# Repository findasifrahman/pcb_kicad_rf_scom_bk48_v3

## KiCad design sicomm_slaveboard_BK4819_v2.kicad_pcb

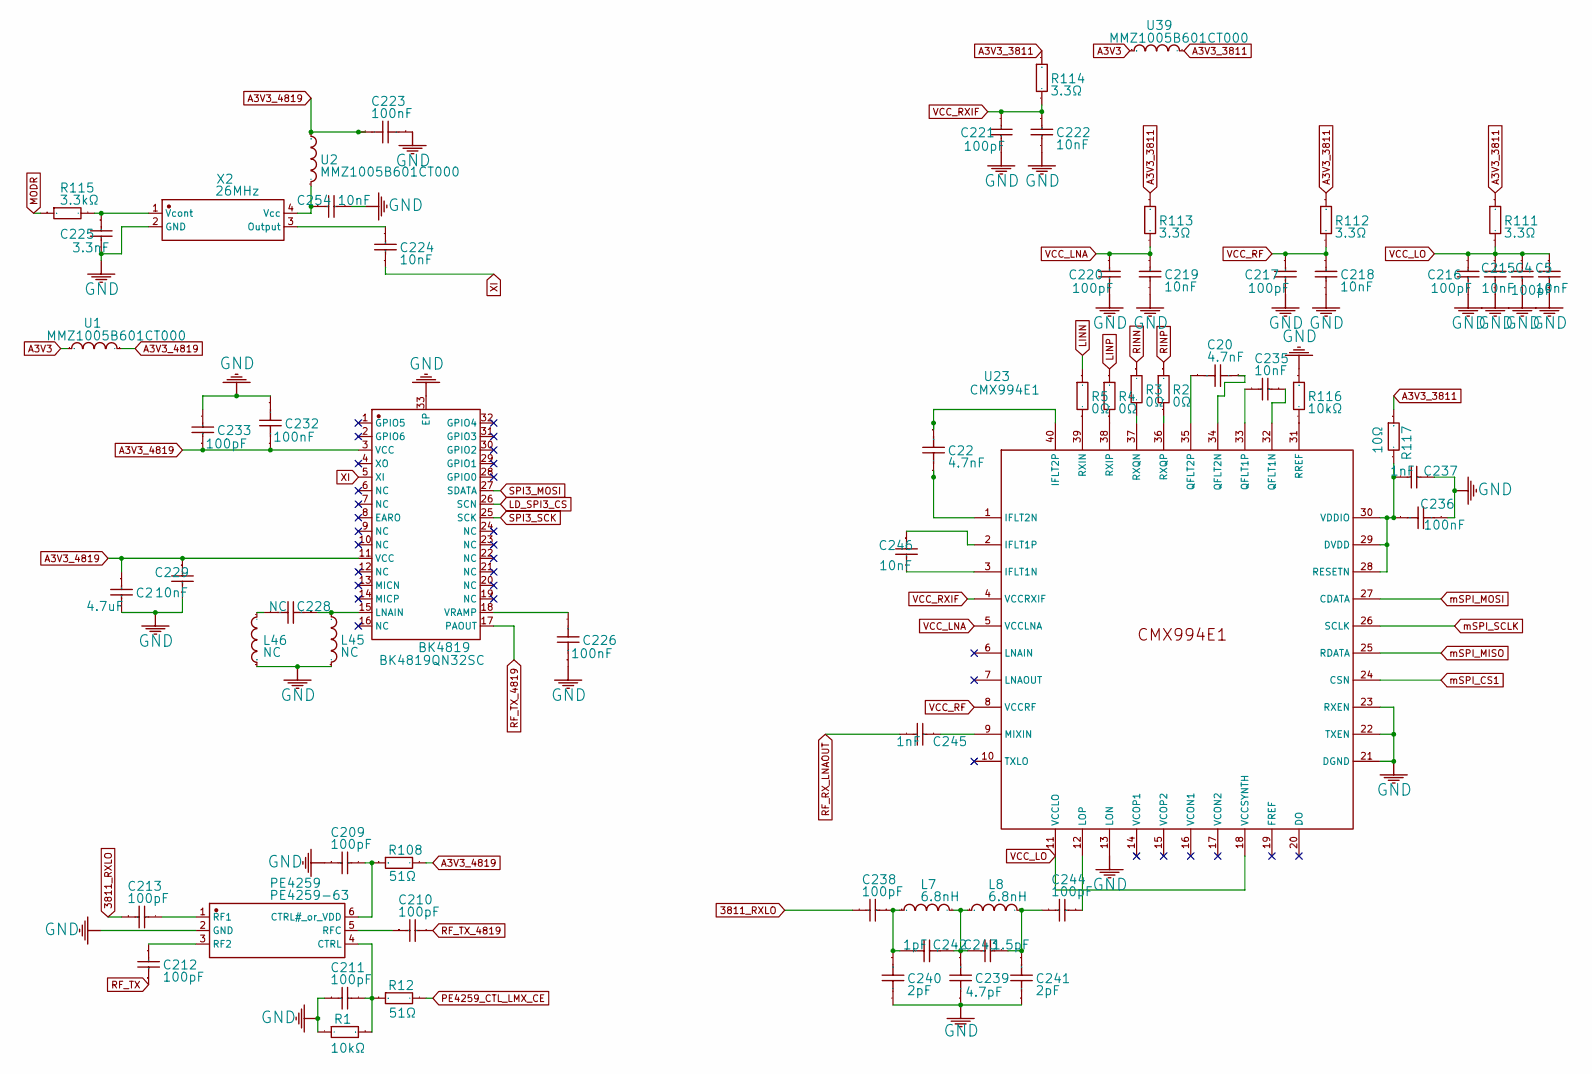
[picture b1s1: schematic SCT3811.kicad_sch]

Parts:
BK4819: BK4819QN32SC; QFN-32_L4.0-W4.0-P0.40-TL-EP2.9; Manufacturer Part BK4819QN32SC
C2: 4.7uF; C0402; Manufacturer Part CL05A475MP5NRNC
C4, C209, C210, C211, C212, C213, C216, C217, C220, C221, C233, C238, C244: 100pF; C0402
C5, C215, C218, C219, C222, C235, C246: 10nF; C0402; Manufacturer Part GRM1555C1E103JE01D
C20, C22: 4.7nF; C0402; Manufacturer Part GRM1557U1A472JA01D
C223, C226, C232, C236: 100nF; C0402
C224, C229, C254: 10nF; C0402
C225: 3.3nF; C0603; Manufacturer Part CL10B332KB8NNNC
C228: NC; C0402
C237, C245: 1nF; C0402
C239: 4.7pF; C0402
C240, C241: 2pF; C0402
C242: 1pF; C0402
C243: 1.5pF; C0402
L7, L8: 6.8nH; IND-SMD_L1.0-W0.5-2; Manufacturer Part LQW15AN6N8H00D
L45, L46: NC; L0402
PE4259: PE4259-63; SC-70-6_L2.2-W1.3-P0.65-LS2.1-BL; Manufacturer Part PE4259-63
R1, R116: 10kΩ; R0402
R2, R3, R4, R5: 0Ω; R0402
R12, R108: 51Ω; R0603; Manufacturer Part 0603WAF510JT5E
R111, R112, R113, R114: 3.3Ω; R0402; Manufacturer Part RC0402JR-073R3L
R115: 3.3kΩ; R0402; Manufacturer Part 0402WGF3301TCE
R117: 10Ω; C0402
U1, U2, U39: MMZ1005B601CT000; L0402; Manufacturer Part MMZ1005B601CT000
U23: CMX994E1; QFN50P600X600X100-41N-D
X2: 26MHz; OSC-SMD_4P-L3.2-W2.5-BL_1XTV; Manufacturer Part 1XTV26000PEA

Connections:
3811_RXLO: C213.1, C238.2
A3V3: U1.1, U39.1; also elsewhere on the board
A3V3_3811: R111.1, R112.1, R113.1, R117.1, U39.2; also elsewhere on the board
A3V3_4819: BK4819.3 (VCC), BK4819.11 (VCC), C2.1, C223.2, C229.1, C232.1, C233.1, R108.2, U1.2, U2.1
GND: BK4819.33 (EP), C2.2, C4.1, C5.2, C209.1, C211.1, C215.2, C216.1, C217.1, C218.2, C219.2, C220.1, C221.1, C222.2, C223.1, C225.2, C226.1, C229.2, C232.2, C233.2, C236.2, C237.1, C239.2, C240.2, C241.2, C254.2, L45.2, L46.1, PE4259.2 (GND), R1.2, R116.1, U23.13 (LON), U23.21 (DGND), U23.22 (TXEN), U23.23 (RXEN), U23.41, X2.2 (GND); also elsewhere on the board
LD_SPI3_CS: BK4819.26 (SCN); also elsewhere on the board
LINN: R5.1; also elsewhere on the board
LINP: R4.1; also elsewhere on the board
MODR: R115.1; also elsewhere on the board
unnamed: BK4819.15 (LNAIN), C228.1, L45.1
unnamed: BK4819.18 (VRAMP), C226.2
unnamed 17: C239.1, C242.1, L7.2, L8.1; also elsewhere on the board
unnamed 18: C241.1, C244.2, L8.2; also elsewhere on the board
unnamed: C228.2, L46.2
unnamed: C238.1, C240.1, C242.2, L7.1
unnamed: C209.2, PE4259.6 (CTRL#_or_VDD), R108.1
unnamed: C211.2, PE4259.4 (CTRL), R1.1, R12.1
unnamed: C213.2, PE4259.1 (RF1)
unnamed: C212.2, PE4259.3 (RF2)
unnamed: C210.1, PE4259.5 (RFC)
unnamed: C236.1, C237.2, R117.2, U23.28 (RESETN), U23.29 (DVDD), U23.30 (VDDIO)
unnamed: C246.2, U23.3 (IFLT1N)
unnamed: C246.1, U23.2 (IFLT1P)
unnamed: C22.2, U23.1 (IFLT2N)
unnamed: C22.1, U23.40 (IFLT2P)
unnamed: C244.1, U23.12 (LOP)
unnamed: C245.1, U23.9 (MIXIN)
unnamed: C235.1, U23.32 (QFLT1N)
unnamed: C235.2, U23.33 (QFLT1P)
unnamed: C20.2, U23.34 (QFLT2N)
unnamed: C20.1, U23.35 (QFLT2P)
unnamed: R116.2, U23.31 (RREF)
unnamed: R5.2, U23.39 (RXIN)
unnamed: R4.2, U23.38 (RXIP)
unnamed: R3.2, U23.37 (RXQN)
unnamed: R2.2, U23.36 (RXQP)
unnamed 60: X2.3 (Output); also elsewhere on the board
unnamed: C254.1, U2.2, X2.4 (Vcc)
unnamed: C225.1, R115.2, X2.1 (Vcont)
PE4259_CTL_LMX_CE: R12.2; also elsewhere on the board
RF_RX_LNAOUT: C245.2; also elsewhere on the board
RF_TX: C212.1; also elsewhere on the board
RF_TX_4819: BK4819.17 (PAOUT), C210.2
RINN: R3.1; also elsewhere on the board
RINP: R2.1; also elsewhere on the board
SPI3_MOSI: BK4819.27 (SDATA); also elsewhere on the board
SPI3_SCK: BK4819.25 (SCK); also elsewhere on the board
VCC_LNA: C219.1, C220.2, R113.2, U23.5 (VCCLNA)
VCC_LO: C4.2, C5.1, C215.1, C216.2, R111.2, U23.11 (VCCLO), U23.18 (VCCSYNTH)
VCC_RF: C217.2, C218.1, R112.2, U23.8 (VCCRF)
VCC_RXIF: C221.2, C222.1, U23.4 (VCCRXIF); also elsewhere on the board
XI: BK4819.5 (XI); also elsewhere on the board
mSPI_CS1: U23.24 (CSN); also elsewhere on the board
mSPI_MISO: U23.25 (RDATA); also elsewhere on the board
mSPI_MOSI: U23.27 (CDATA); also elsewhere on the board
mSPI_SCLK: U23.26 (SCLK); also elsewhere on the board

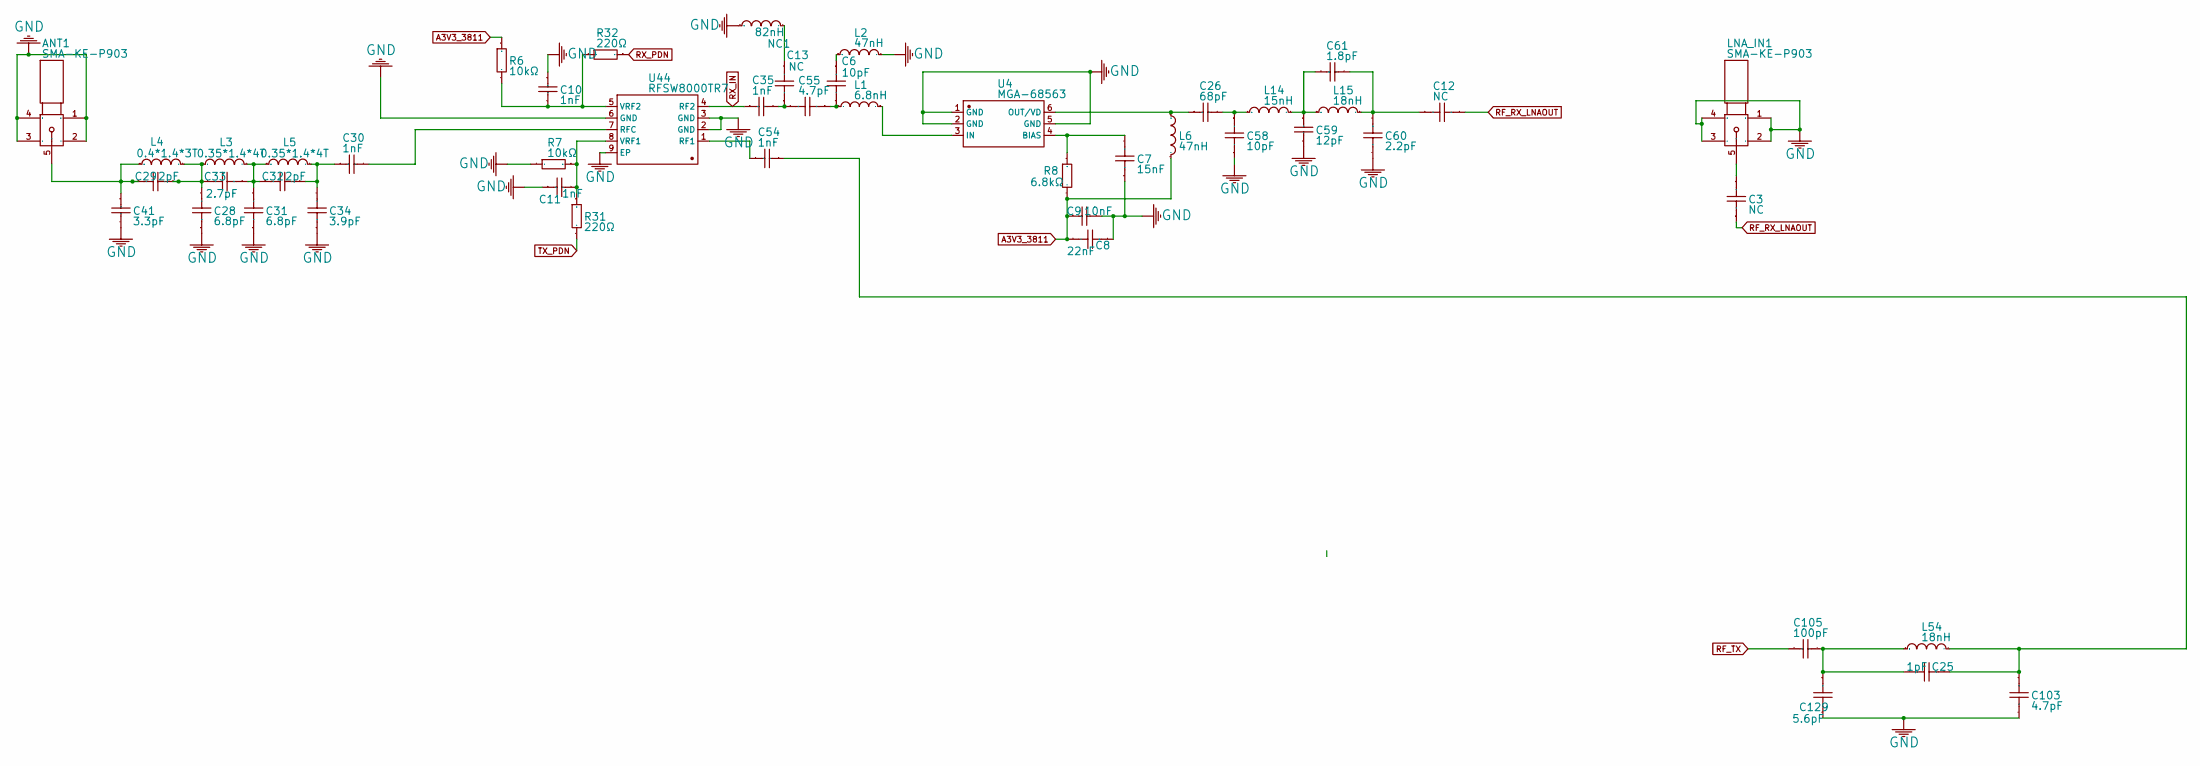
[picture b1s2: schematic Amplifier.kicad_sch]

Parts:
ANT1: SMA-KE-P903; SMA-TH_SMA-KE-P903
C3, C12: NC; C0402
C6, C58: 10pF; C0402
C7: 15nF; C0402; Manufacturer Part TCC0402X7R153K250AT
C8: 22nF; C0402; Manufacturer Part CL05B223KA5NNNC
C9: 10nF; C0402; Manufacturer Part GRM1555C1E103JE01D
C10, C11, C30, C35, C54: 1nF; C0402
C13: NC; C0603
C25: 1pF; C0402
C26: 68pF; C0402; Manufacturer Part GRM1555C1H680JA01D
C28, C31: 6.8pF; C0603; Manufacturer Part CC0603CRNPO9BN6R8
C29, C32: 2pF; C0402
C33: 2.7pF; C0603; Manufacturer Part 0603CG2R7C500NT
C34: 3.9pF; C0402
C41: 3.3pF; C0603; Manufacturer Part 0603CG3R3C500NT
C55, C103: 4.7pF; C0402
C59: 12pF; C0402
C60: 2.2pF; C0402; Manufacturer Part GJM1555C1H2R2CB01D
C61: 1.8pF; C0603; Manufacturer Part CL10C1R8BB8NNNC
C105: 100pF; C0402
C129: 5.6pF; C0402
L1: 6.8nH; IND-SMD_L1.6-W0.8-RD; Manufacturer Part LQW18AN6N8C10D
L2, L6: 47nH; IND-SMD_L1.6-W0.8-RD; Manufacturer Part LQG18HN47NJ00D
L3, L5: 0.35*1.4*4T; IND-SMD_L2.3-W1.7-1
L4: 0.4*1.4*3T; IND-SMD_L2.3-W1.7-1
L14: 15nH; IND-SMD_L1.0-W0.6
L15, L54: 18nH; IND-SMD_L1.6-W0.8-RD; Manufacturer Part LQG18HN18NJ00D
LNA_IN1: SMA-KE-P903; SMA-TH_SMA-KE-P903
NC1: 82nH; C0603; Manufacturer Part NC
R6, R7: 10kΩ; R0402
R8: 6.8kΩ; R0805; Manufacturer Part 0805W8F6801T5E
R31, R32: 220Ω; R0603; Manufacturer Part 0603WAF2200T5E
U4: MGA-68563; SOT-363_L2.0-W1.3-P0.65-LS2.1-BL; Manufacturer Part mga-68563
U44: RFSW8000TR7; DFN-8_L2.0-W2.0-P0.50-BL-EP; Manufacturer Part RFSW8000TR7

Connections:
A3V3_3811: C8.2, C9.1, L6.2, R6.1, R8.2; also elsewhere on the board
GND: ANT1.1, ANT1.2, ANT1.3, ANT1.4, C7.1, C8.1, C9.2, C10.1, C11.1, C28.1, C31.1, C34.1, C41.2, C58.2, C59.2, C60.2, C103.2, C129.2, L2.2, LNA_IN1.1, LNA_IN1.2, LNA_IN1.3, LNA_IN1.4, NC1.1, R7.2, U4.1 (GND), U4.2 (GND), U4.5 (GND), U44.2 (GND), U44.3 (GND), U44.6 (GND), U44.9 (EP); also elsewhere on the board
unnamed: ANT1.5, C29.1, C41.1, L4.1
unnamed: C3.2, LNA_IN1.5
unnamed: C6.1, L2.1
unnamed: C12.2, C60.1, C61.2, L15.2
unnamed: C13.1, C35.2, C55.2
unnamed: C13.2, NC1.2
unnamed: C26.2, C58.1, L14.1
unnamed: C28.2, C29.2, C33.1, L3.1, L4.2
unnamed: C30.1, C32.2, C34.2, L5.2
unnamed: C31.2, C32.1, C33.2, L3.2, L5.1
unnamed: C6.2, C55.1, L1.2
unnamed: C59.1, C61.1, L14.2, L15.1
unnamed: C25.1, C54.2, C103.1, L54.2
unnamed: C25.2, C105.2, C129.1, L54.1
unnamed: C7.2, R8.1, U4.4 (BIAS)
unnamed: L1.1, U4.3 (IN)
unnamed: C26.1, L6.1, U4.6 (OUT/VD)
unnamed: C54.1, U44.1 (RF1)
unnamed: C30.2, U44.7 (RFC)
unnamed: C11.2, R7.1, R31.1, U44.8 (VRF1)
unnamed: C10.2, R6.2, R32.2, U44.5 (VRF2)
RF_RX_LNAOUT: C3.1, C12.1; also elsewhere on the board
RF_TX: C105.1; also elsewhere on the board
RX_IN: C35.1, U44.4 (RF2)
RX_PDN: R32.1; also elsewhere on the board
TX_PDN: R31.2; also elsewhere on the board

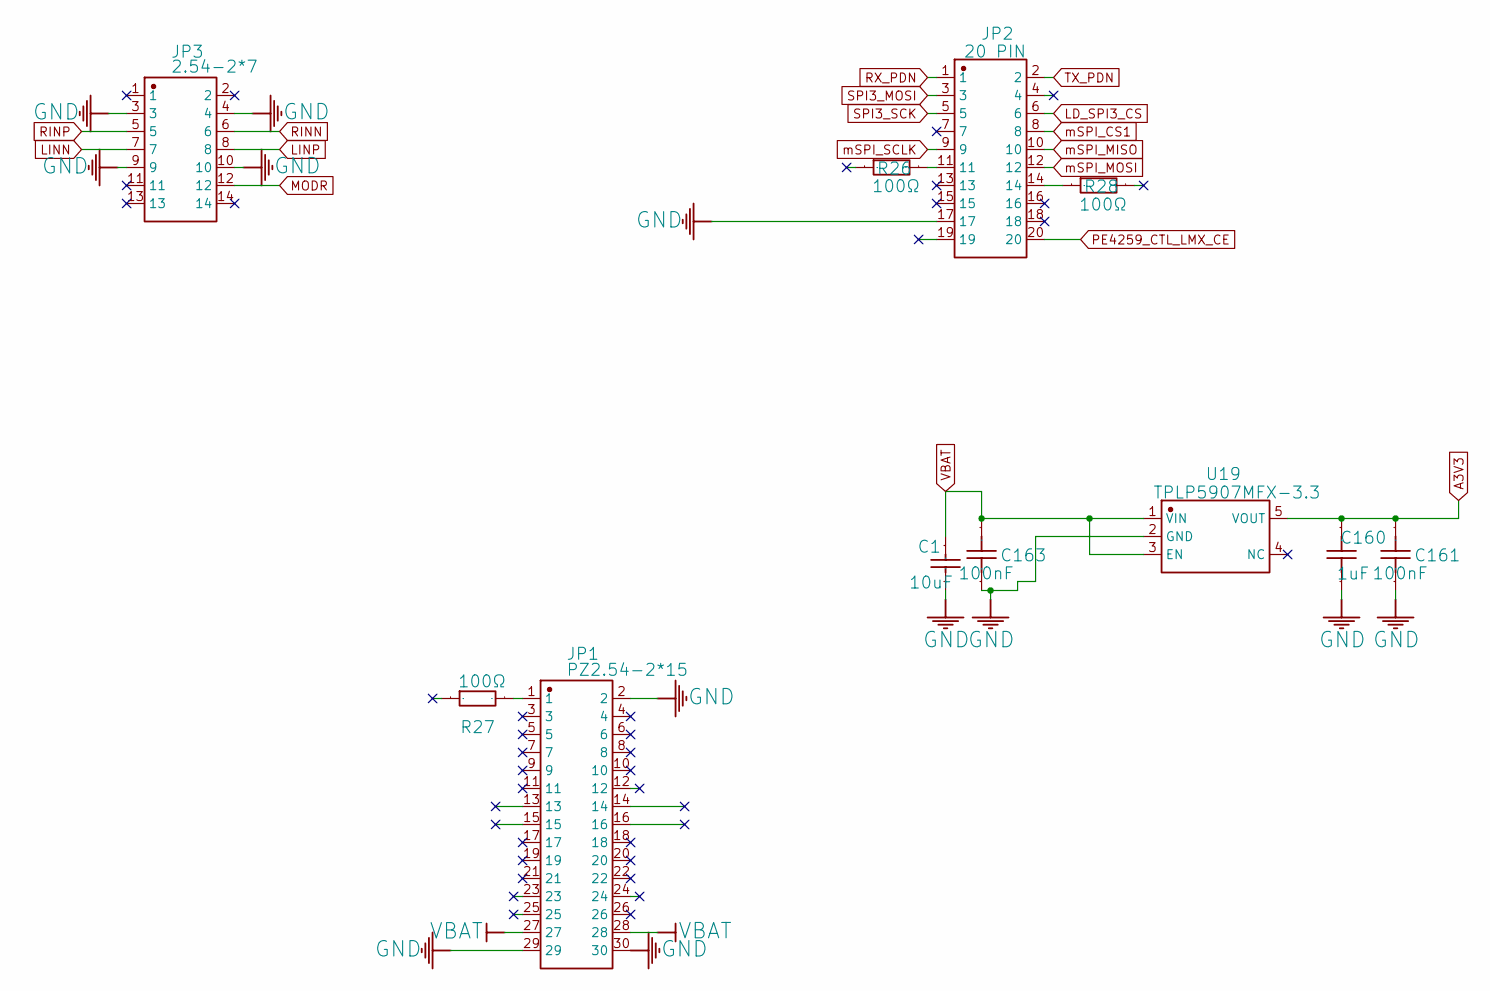
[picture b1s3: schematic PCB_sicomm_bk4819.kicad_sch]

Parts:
C1: 10uF; C0402; Manufacturer Part CL05A106MQ5NUNC
C160: 1uF; C0402
C161, C163: 100nF; C0402
JP1: PZ2.54-2*15; HDR-TH_30P-P2.54-V-M-R2-C15-S2.54-2; Manufacturer Part PZ2.54-2*15
JP2: 20 PIN; HDR-TH_20P-P2.54-V-M-R2-C10-S2.54; Manufacturer Part 2.54-2*10
JP3: 2.54-2*7; HDR-TH_14P-P2.54-V-M-R2-C7-S2.54; Manufacturer Part 2.54-2*7
R26, R27: 100Ω; R0402; Manufacturer Part 0402WGF1000TCE
R28: 100Ω; C0402; Manufacturer Part 0402WGF1000TCE
U19: TPLP5907MFX-3.3; SOT-23-5_L2.9-W1.6-P0.95-LS2.8-BR

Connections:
A3V3: C160.1, C161.2, U19.5 (VOUT); also elsewhere on the board
GND: C1.2, C160.2, C161.1, C163.1, JP1.2, JP1.29, JP1.30, JP2.17, JP3.3, JP3.4, JP3.9, JP3.10, U19.2 (GND); also elsewhere on the board
LD_SPI3_CS: JP2.6; also elsewhere on the board
LINN: JP3.7; also elsewhere on the board
LINP: JP3.8; also elsewhere on the board
MODR: JP3.12; also elsewhere on the board
unnamed: JP1.1, R27.2
unnamed: JP2.11, R26.2
unnamed: JP2.14, R28.1
PE4259_CTL_LMX_CE: JP2.20; also elsewhere on the board
RINN: JP3.6; also elsewhere on the board
RINP: JP3.5; also elsewhere on the board
RX_PDN: JP2.1; also elsewhere on the board
SPI3_MOSI: JP2.3; also elsewhere on the board
SPI3_SCK: JP2.5; also elsewhere on the board
TX_PDN: JP2.2; also elsewhere on the board
VBAT: C1.1, C163.2, JP1.27, JP1.28, U19.1 (VIN), U19.3 (EN)
mSPI_CS1: JP2.8; also elsewhere on the board
mSPI_MISO: JP2.10; also elsewhere on the board
mSPI_MOSI: JP2.12; also elsewhere on the board
mSPI_SCLK: JP2.9; also elsewhere on the board

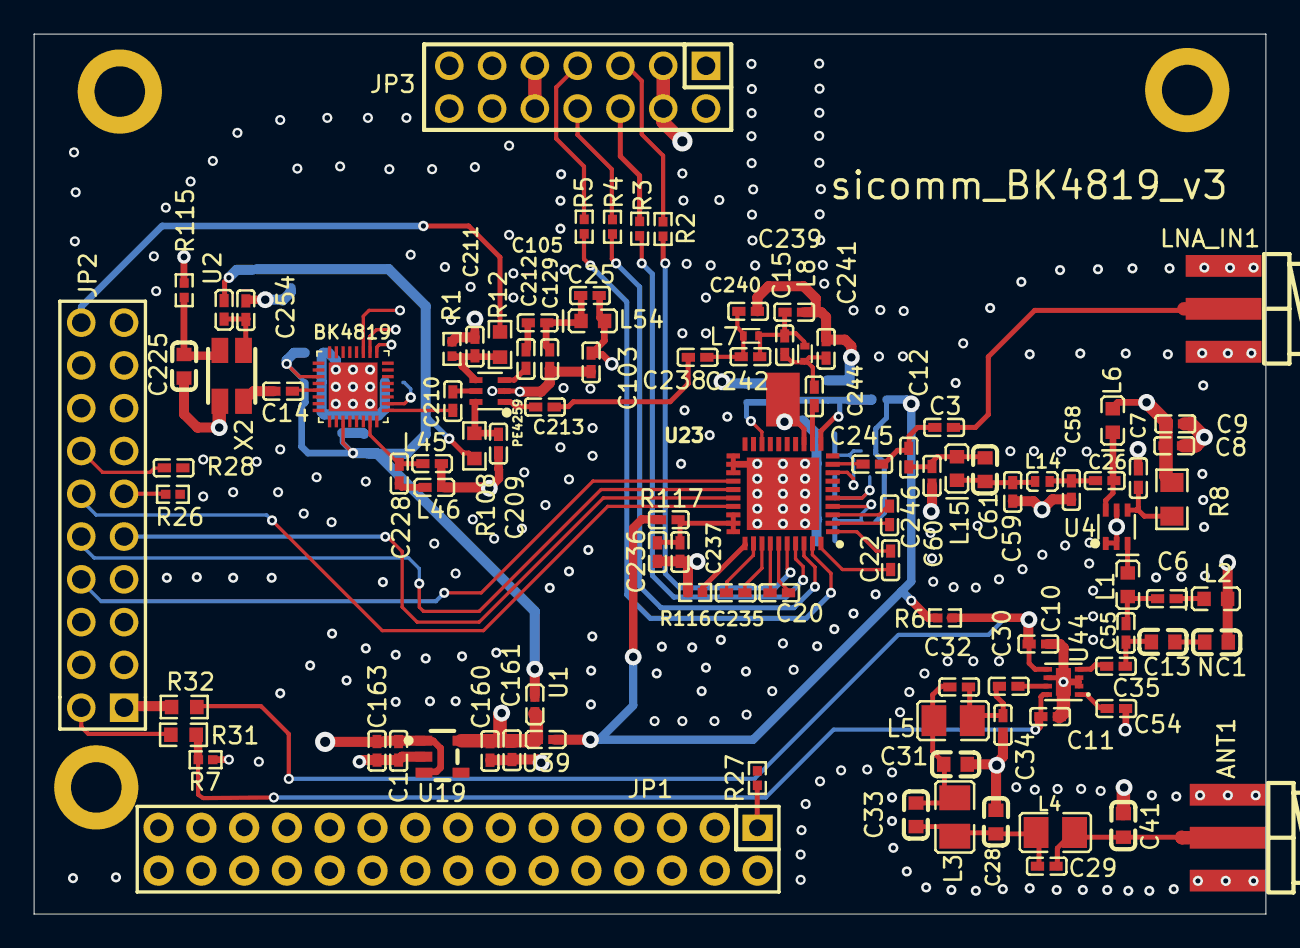
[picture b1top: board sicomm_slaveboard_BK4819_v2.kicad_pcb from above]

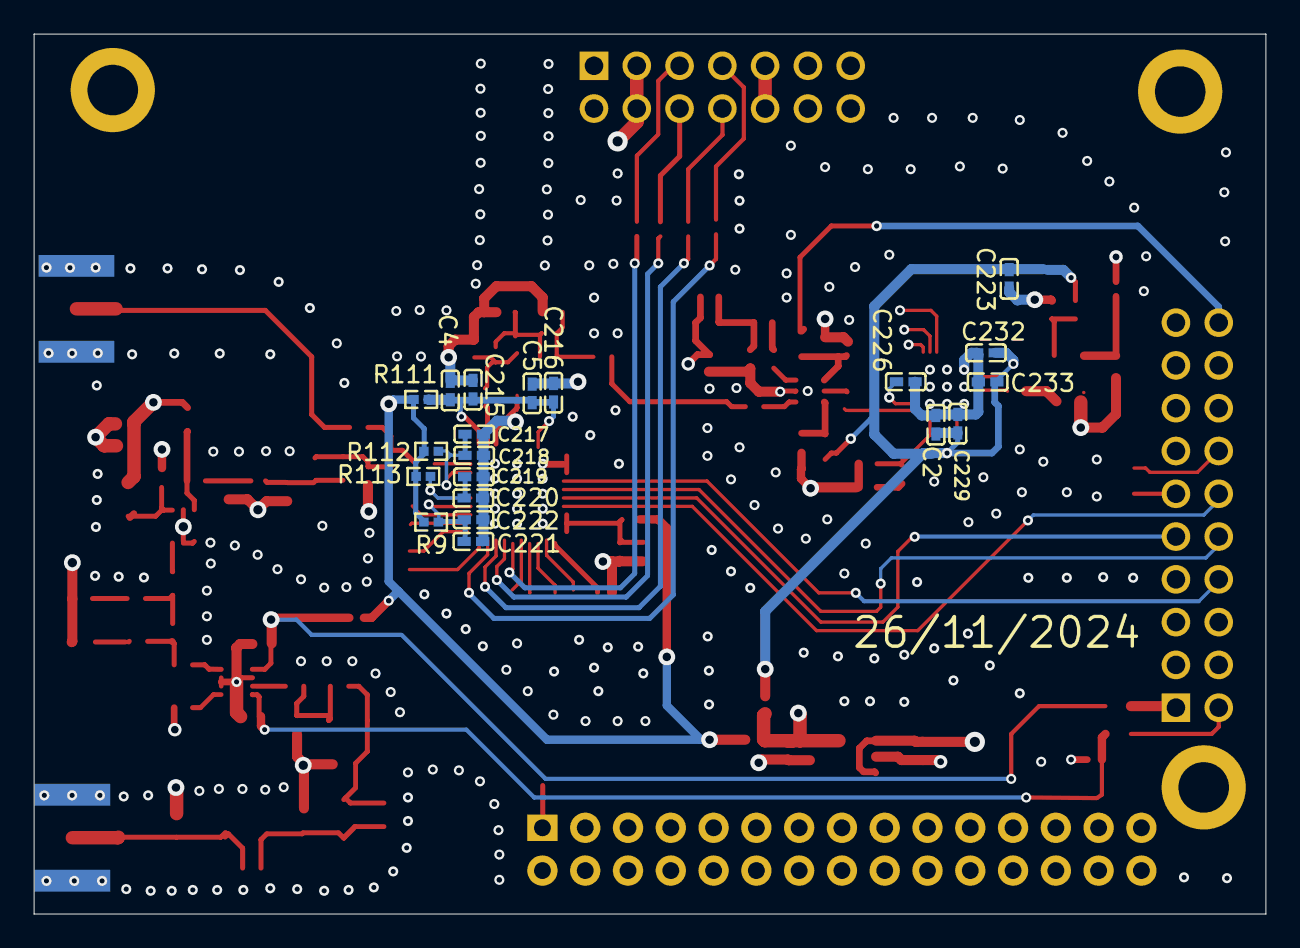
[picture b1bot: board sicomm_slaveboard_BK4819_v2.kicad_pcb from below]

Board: 4 copper layers, 73.1 x 52.2 mm, 127 parts (20 on the bottom side), 84 nets.

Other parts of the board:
C14: 10nF; C0402
C15: 1.5pF; C0402
Pad_gge111627: Pad_gge111627
Pad_gge189569: Pad_gge189569
Pad_gge257249: Pad_gge257249
Pad_gge303765: Pad_gge303765
R9: 3.3Ω; R0402

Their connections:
A3V3_3811: R9.1; also elsewhere on the board
GND: Pad_gge111627.1, Pad_gge189569.1, Pad_gge257249.4, Pad_gge303765.1; also elsewhere on the board
unnamed 17: C15.1; also elsewhere on the board
unnamed 18: C15.2; also elsewhere on the board
unnamed 60: C14.1; also elsewhere on the board
VCC_RXIF: R9.2; also elsewhere on the board
XI: C14.2; also elsewhere on the board

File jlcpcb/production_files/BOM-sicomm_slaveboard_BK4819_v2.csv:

Comment,Designator,Footprint,LCSC,Quantity
Pad_gge255906,Pad_gge255906,Pad_gge255906,,1
Pad_gge257249,Pad_gge257249,Pad_gge257249,,1
4.7uF,C2,C0402,,1
100nF,C223,C0402,,1
100nF,C226,C0402,,1
10nF,C229,C0402,,1
100nF,C232,C0402,,1
100pF,C233,C0402,,1
100pF,C4,C0402,,1
10nF,C5,C0402,,1
10nF,C215,C0402,,1
100pF,C216,C0402,,1
100pF,C217,C0402,,1
10nF,C218,C0402,,1
10nF,C219,C0402,,1
100pF,C220,C0402,,1
100pF,C221,C0402,,1
10nF,C222,C0402,,1
3.3Ω,R111,R0402,,1
3.3Ω,R112,R0402,,1
3.3Ω,R113,R0402,,1
3.3Ω,R114,R0402,,1
10kΩ,R6,R0402,,1
15nF,C7,C0402,,1
NC,C13,C0402,,1
47nH,L6,IND-SMD_L1.6-W0.8-RD,,1
6.8kΩ,R8,R0805,,1
MGA-68563,U4,SOT-363_L2.0-W1.3-P0.65-LS2.1-BL,,1
NC,C3,C0402,,1
NC,C12,C0402,,1
MMZ1005B601CT000,U2,L0402,,1
68pF,C26,C0402,,1
26MHz,X2,OSC-SMD_4P-L3.2-W2.5-BL,,1
BK4819QN32SC,BK4819,QFN-32_L4.0-W4.0-P0.40-TL-EP2.9,,1
1pF,C25,C0402,,1
100pF,C209,C0402,,1
100pF,C210,C0402,,1
100pF,C211,C0402,,1
100pF,C212,C0402,,1
100pF,C213,C0402,,1
10nF,C224,C0402,,1
3.3nF,C225,C0603,,1
NC,C228,C0402,,1
10nF,C254,C0402,,1
NC,L45,L0402,,1
NC,L46,L0402,,1
PE4259-63,PE4259,SC-70-6_L2.2-W1.3-P0.65-LS2.1-BL,,1
10kΩ,R1,R0402,,1
51Ω,R12,R0603,,1
51Ω,R108,R0603,,1
3.3kΩ,R115,R0402,,1
1nF,C10,C0402,,1
1nF,C11,C0402,,1
10kΩ,R7,R0402,,1
22nF,C8,C0402,,1
10nF,C9,C0402,,1
10pF,C6,C0402,,1
47nH,L2,IND-SMD_L1.6-W0.8-RD,,1
MMZ1005B601CT000,U1,L0402,,1
10uF,C1,C0402,,1
4.7nF,C20,C0402,,1
4.7nF,C22,C0402,,1
6.8pF,C28,C0603,,1
2pF,C29,C0402,,1
1nF,C30,C0402,,1
6.8pF,C31,C0603,,1
2pF,C32,C0402,,1
2.7pF,C33,C0603,,1
3.9pF,C34,C0402,,1
1nF,C35,C0402,,1
3.3pF,C41,C0603,,1
1nF,C54,C0402,,1
4.7pF,C55,C0402,,1
10pF,C58,C0402,,1
12pF,C59,C0402,,1
2.2pF,C60,C0402,,1
1.8pF,C61,C0603,,1
4.7pF,C103,C0402,,1
100pF,C105,C0402,,1
5.6pF,C129,C0402,,1
1uF,C160,C0402,,1
100nF,C161,C0402,,1
100nF,C163,C0402,,1
10nF,C235,C0402,,1
100nF,C236,C0402,,1
1nF,C237,C0402,,1
100pF,C238,C0402,,1
4.7pF,C239,C0402,,1
2pF,C240,C0402,,1
2pF,C241,C0402,,1
1pF,C242,C0402,,1
1.5pF,C243,C0402,,1
100pF,C244,C0402,,1
1nF,C245,C0402,,1
10nF,C246,C0402,,1
6.8nH,L1,IND-SMD_L1.6-W0.8-1,,1
0.35*1.4*4T,L3,IND-SMD_L2.3-W1.7-1,,1
0.4*1.4*3T,L4,IND-SMD_L2.3-W1.7-1,,1
0.35*1.4*4T,L5,IND-SMD_L2.3-W1.7-1,,1
6.8nH,L7,IND-SMD_L1.0-W0.5-2,,1
6.8nH,L8,IND-SMD_L1.0-W0.5-2,,1
15nH,L14,IND-SMD_L1.0-W0.6,,1
18nH,L15,IND-SMD_L1.6-W0.8-RD,,1
18nH,L54,IND-SMD_L1.6-W0.8-RD,,1
100Ω,R26,R0402,,1
100Ω,R27,R0402,,1
100Ω,R28,R0402,,1
220Ω,R31,R0603,,1
220Ω,R32,R0603,,1
10kΩ,R116,R0402,,1
10Ω,R117,R0402,,1
TPLP5907MFX-3.3,U19,SOT-23-5_L2.9-W1.6-P0.95-LS2.8-BR,,1
CMX994E1,U23,CMX994E1,,1
MMZ1005B601CT000,U39,L0402,,1
RFSW8000TR7,U44,DFN-8_L2.0-W2.0-P0.50-BL-EP,,1
0Ω,R2,R0402,,1
0Ω,R3,R0402,,1
0Ω,R4,R0402,,1
0Ω,R5,R0402,,1
2.54-2*7,JP3,HDR-TH_14P-P2.54-V-F-R2-C7-S2.54,,1
20 PIN,JP2,HDR-TH_20P-P2.54-V-M-R2-C10-S2.54,,1
PZ2.54-2*15,JP1,HDR-TH_30P-P2.54-V-M-R2-C15-S2.54-2,,1
Pad_gge111627,Pad_gge111627,Pad_gge111627,,1
Pad_gge189569,Pad_gge189569,Pad_gge189569,,1
Pad_gge290440,Pad_gge290440,Pad_gge290440,,1
Pad_gge303765,Pad_gge303765,Pad_gge303765,,1

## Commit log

2024-11-24 sch and pcb
